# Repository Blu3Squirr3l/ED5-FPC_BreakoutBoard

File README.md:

# FFC/FPC Breakout and Extension Board

A simple ffc/fpc breakout board as KiCAD 6 project.
Board size is 46 x 46 mm.

## Files

- `CadModels/`-> 3d models of individual project parts
- `Export/`-> BOM, Gerber &amp; drill files, Pick &amp; Place information
- `ProjectLibrary`-> footprints of individual project parts

## Preview

## Note

To use this board, additional hardware is necessary:
- 25 pin, 0.3mm pitch ffc/fpc cable
- 10 pin, 0.5mm pitch ffc/fpc cable

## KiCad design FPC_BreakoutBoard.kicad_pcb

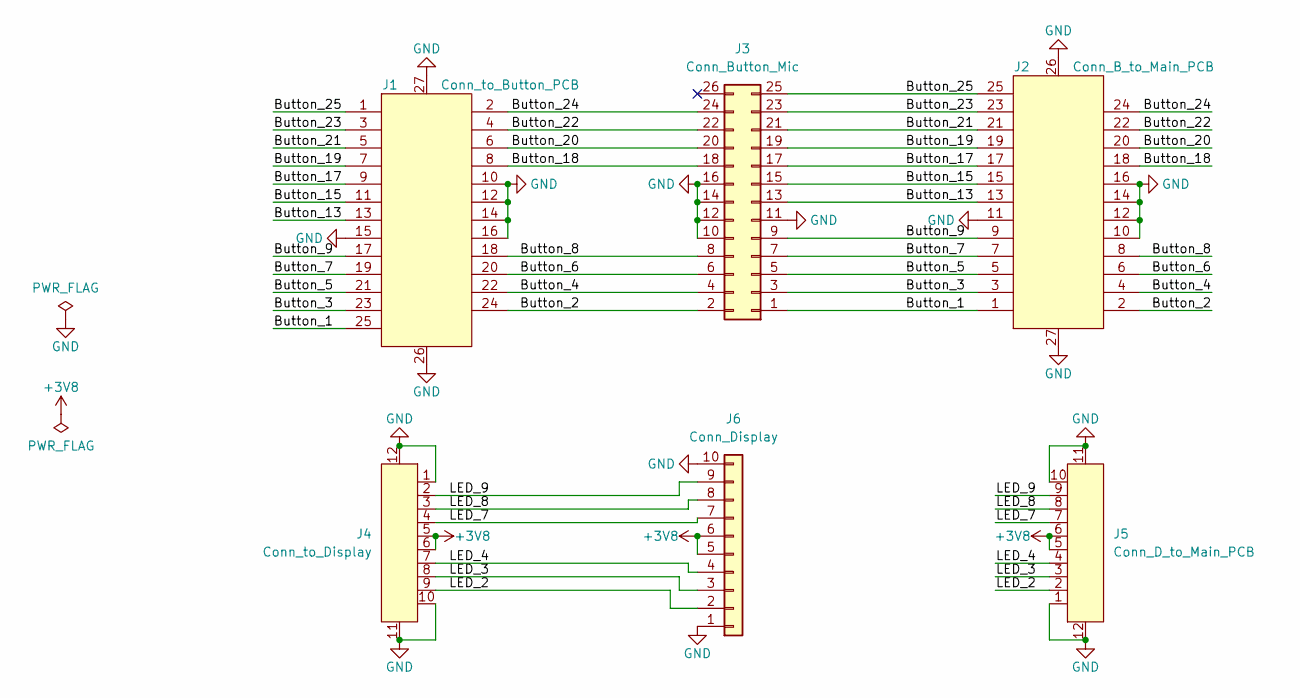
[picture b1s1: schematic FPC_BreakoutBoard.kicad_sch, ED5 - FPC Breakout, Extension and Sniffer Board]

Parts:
J1: Conn_to_Button_PCB; FH35C-25S-0.3SHW; Manufacturer_Part_Number FH35C-25S-0.3SHW(50); LCSC part number C424661
J2: Conn_B_to_Main_PCB; FH35C-25S-0.3SHW; Manufacturer_Part_Number FH35C-25S-0.3SHW(50); LCSC part number C424661
J3: Conn_Button_Mic; PinHeader_2x13_P2.54mm_Vertical
J4: Conn_to_Display; HDGC_0.5K-HX-10PWB_1x10_P0.50mm_Horizontal; Manufacturer_Part_Number 0.5K-HX-10PWB; LCSC part number C2919493
J5: Conn_D_to_Main_PCB; HDGC_0.5K-HX-10PWB_1x10_P0.50mm_Horizontal; Manufacturer_Part_Number 0.5K-HX-10PWB; LCSC part number C2919493
J6: Conn_Display; PinHeader_1x10_P2.54mm_Vertical

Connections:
+3V8: J4.5, J4.6, J5.5, J5.6, J6.5, J6.6
/Button_1: J1.25, J2.1, J3.1
/Button_2: J1.24, J2.2, J3.2
/Button_3: J1.23, J2.3, J3.3
/Button_4: J1.22, J2.4, J3.4
/Button_5: J1.21, J2.5, J3.5
/Button_6: J1.20, J2.6, J3.6
/Button_7: J1.19, J2.7, J3.7
/Button_8: J1.18, J2.8, J3.8
/Button_9: J1.17, J2.9, J3.9
/Button_13: J1.13, J2.13, J3.13
/Button_15: J1.11, J2.15, J3.15
/Button_17: J1.9, J2.17, J3.17
/Button_18: J1.8, J2.18, J3.18
/Button_19: J1.7, J2.19, J3.19
/Button_20: J1.6, J2.20, J3.20
/Button_21: J1.5, J2.21, J3.21
/Button_22: J1.4, J2.22, J3.22
/Button_23: J1.3, J2.23, J3.23
/Button_24: J1.2, J2.24, J3.24
/Button_25: J1.1, J2.25, J3.25
/LED_2: J4.9, J5.2, J6.2
/LED_3: J4.8, J5.3, J6.3
/LED_4: J4.7, J5.4, J6.4
/LED_7: J4.4, J5.7, J6.7
/LED_8: J4.3, J5.8, J6.8
/LED_9: J4.2, J5.9, J6.9
GND: J1.10, J1.12, J1.14, J1.15, J1.16, J1.26, J1.27, J2.10, J2.11, J2.12, J2.14, J2.16, J2.26, J2.27, J3.10, J3.11, J3.12, J3.14, J3.16, J4.1, J4.10, J4.11, J4.12, J5.1, J5.10, J5.11, J5.12, J6.1, J6.10

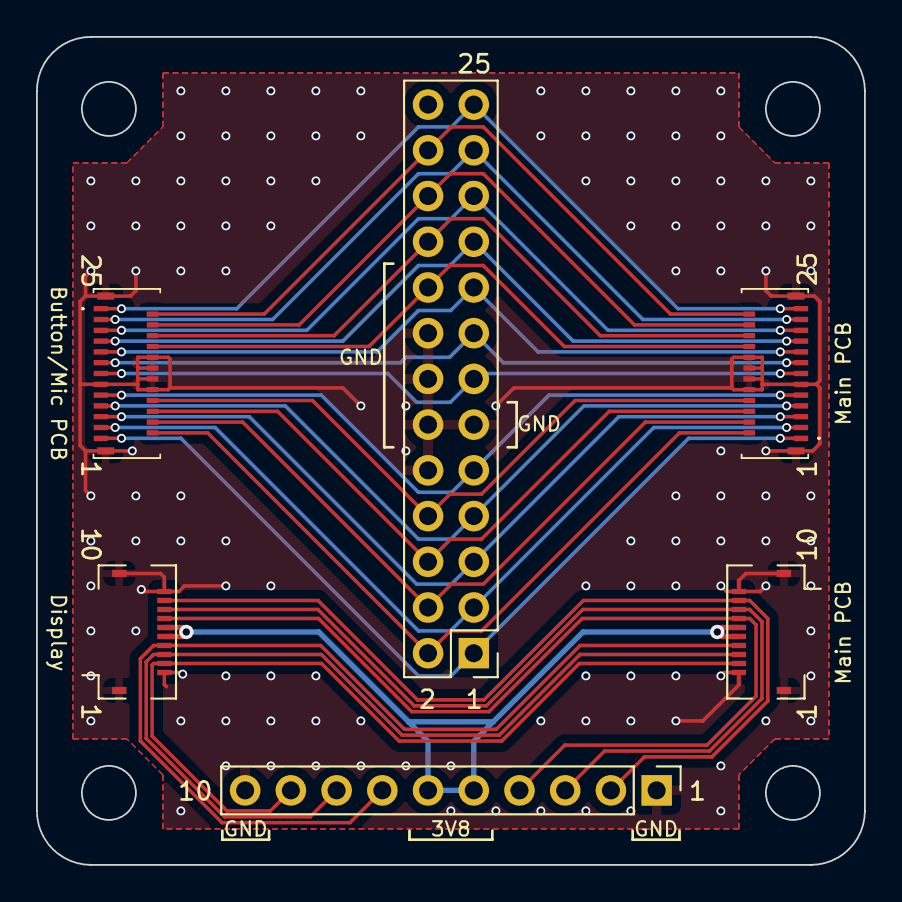
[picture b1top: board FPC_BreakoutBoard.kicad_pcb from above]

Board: 2 copper layers, 46.0 x 46.0 mm, 6 parts (0 on the bottom side), 28 nets.

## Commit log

2023-01-05 identified 3V8 and GND pins; remapped pins + wiring
